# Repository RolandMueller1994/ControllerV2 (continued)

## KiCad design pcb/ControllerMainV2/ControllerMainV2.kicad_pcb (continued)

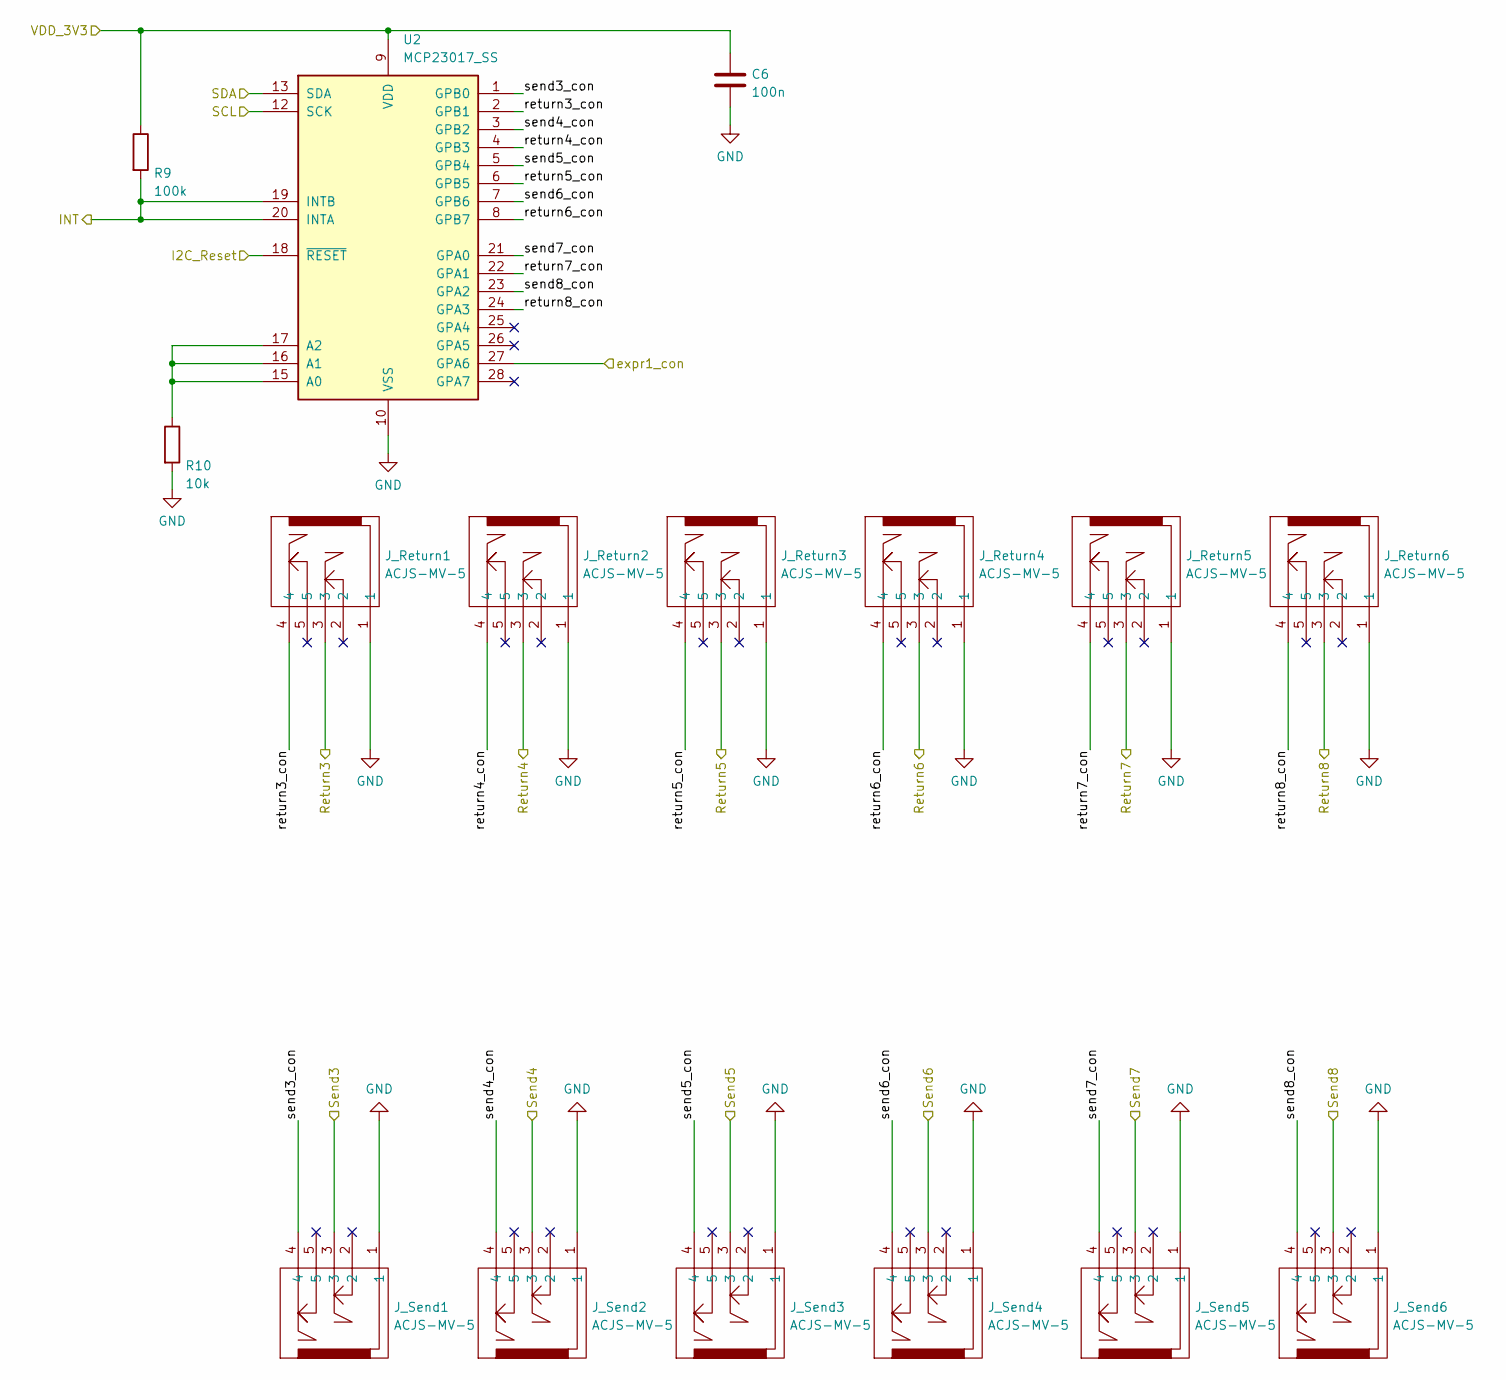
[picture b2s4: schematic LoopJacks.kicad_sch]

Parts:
C6: 100n; C_1206_3216Metric_Pad1.33x1.80mm_HandSolder
J_Return1, J_Return2, J_Return3, J_Return4, J_Return5, J_Return6: ACJS-MV-5; ACJSMV5; Manufacturer_Part_Number ACJS-MV-5; Mouser Part Number 523-ACJS-MV-5
J_Send1, J_Send2, J_Send3, J_Send4, J_Send5, J_Send6: ACJS-MV-5; ACJSMV5; Manufacturer_Part_Number ACJS-MV-5; Mouser Part Number 523-ACJS-MV-5
R9: 100k; R_0805_2012Metric_Pad1.20x1.40mm_HandSolder
R10: 10k; R_0805_2012Metric_Pad1.20x1.40mm_HandSolder
U2: MCP23017_SS; SSOP-28_5.3x10.2mm_P0.65mm

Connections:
/I2C_Reset: U2.18 (~RESET); also elsewhere on the board
/INT: R9.2, U2.19 (INTB), U2.20 (INTA); also elsewhere on the board
/LoopJacks/expr1_con: U2.27 (GPA6); also elsewhere on the board
/LoopJacks/return3_con: J_Return1.4, U2.2 (GPB1)
/LoopJacks/return4_con: J_Return2.4, U2.4 (GPB3)
/LoopJacks/return5_con: J_Return3.4, U2.6 (GPB5)
/LoopJacks/return6_con: J_Return4.4, U2.8 (GPB7)
/LoopJacks/return7_con: J_Return5.4, U2.22 (GPA1)
/LoopJacks/return8_con: J_Return6.4, U2.24 (GPA3)
/LoopJacks/send3_con: J_Send1.4, U2.1 (GPB0)
/LoopJacks/send4_con: J_Send2.4, U2.3 (GPB2)
/LoopJacks/send5_con: J_Send3.4, U2.5 (GPB4)
/LoopJacks/send6_con: J_Send4.4, U2.7 (GPB6)
/LoopJacks/send7_con: J_Send5.4, U2.21 (GPA0)
/LoopJacks/send8_con: J_Send6.4, U2.23 (GPA2)
/SCL: U2.12 (SCK); also elsewhere on the board
/SDA: U2.13 (SDA); also elsewhere on the board
/VDD_3V3: C6.1, R9.1, U2.9 (VDD); also elsewhere on the board
/return3: J_Return1.3; also elsewhere on the board
/return4: J_Return2.3; also elsewhere on the board
/return5: J_Return3.3; also elsewhere on the board
/return6: J_Return4.3; also elsewhere on the board
/return7: J_Return5.3; also elsewhere on the board
/return8: J_Return6.3; also elsewhere on the board
/send3: J_Send1.3; also elsewhere on the board
/send4: J_Send2.3; also elsewhere on the board
/send5: J_Send3.3; also elsewhere on the board
/send6: J_Send4.3; also elsewhere on the board
/send7: J_Send5.3; also elsewhere on the board
/send8: J_Send6.3; also elsewhere on the board
GND: C6.2, J_Return1.1, J_Return2.1, J_Return3.1, J_Return4.1, J_Return5.1, J_Return6.1, J_Send1.1, J_Send2.1, J_Send3.1, J_Send4.1, J_Send5.1, J_Send6.1, R10.2, U2.10 (VSS); also elsewhere on the board
unnamed: R10.1, U2.15 (A0), U2.16 (A1), U2.17 (A2)

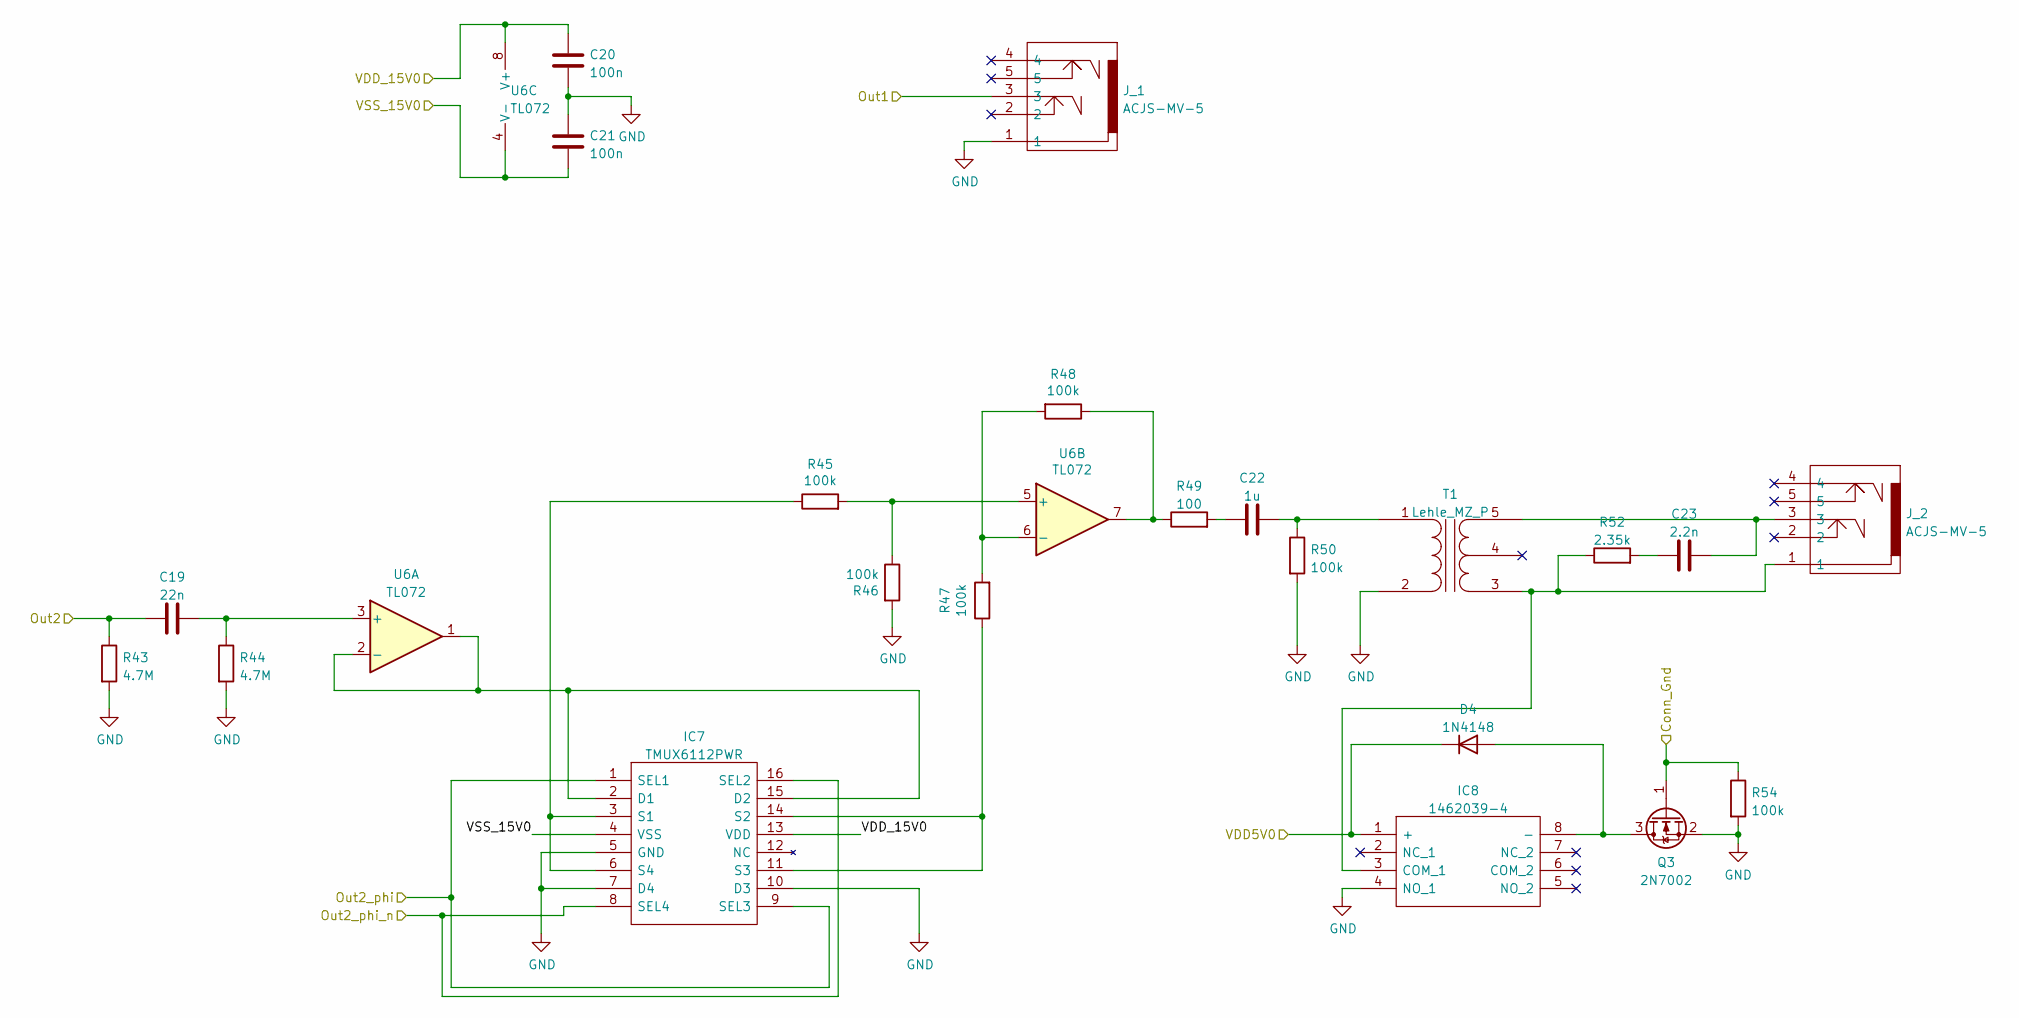
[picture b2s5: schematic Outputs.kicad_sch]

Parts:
C19: 22n; C_1206_3216Metric_Pad1.33x1.80mm_HandSolder
C20, C21: 100n; C_1206_3216Metric_Pad1.33x1.80mm_HandSolder
C22: 1u; C_1206_3216Metric_Pad1.33x1.80mm_HandSolder
C23: 2.2n; C_1206_3216Metric_Pad1.33x1.80mm_HandSolder
D4: 1N4148; D_SOD-123
IC7: TMUX6112PWR; SOP65P640X120-16N; Manufacturer_Part_Number TMUX6112PWR; Mouser Part Number 595-TMUX6112PWR
IC8: 1462039-4; 14620394; Manufacturer_Part_Number 1462039-4; Mouser Part Number 655-1462039-4
J_1, J_2: ACJS-MV-5; ACJSMV5; Manufacturer_Part_Number ACJS-MV-5; Mouser Part Number 523-ACJS-MV-5
Q3: 2N7002; SOT-23
R43, R44: 4.7M; R_0805_2012Metric_Pad1.20x1.40mm_HandSolder
R45, R46, R47, R48, R50, R54: 100k; R_0805_2012Metric_Pad1.20x1.40mm_HandSolder
R49: 100; R_0805_2012Metric_Pad1.20x1.40mm_HandSolder
R52: 2.35k; R_0805_2012Metric_Pad1.20x1.40mm_HandSolder
T1: Lehle_MZ_P
U6: TL072; SOIC-8_3.9x4.9mm_P1.27mm

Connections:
/ConnGnd: Q3.1 (G), R54.1; also elsewhere on the board
/Out2_phi: IC7.1 (SEL1), IC7.9 (SEL3); also elsewhere on the board
/Out2_phi_n: IC7.8 (SEL4), IC7.16 (SEL2); also elsewhere on the board
/VDD_5V0: D4.1 (K), IC8.1 (+); also elsewhere on the board
/VDD_15V0: C20.2, IC7.13 (VDD), U6.8 (V+); also elsewhere on the board
/VSS_15V0: C21.1, IC7.4 (VSS), U6.4 (V-); also elsewhere on the board
/out1: J_1.3; also elsewhere on the board
/out2: C19.1, R43.1; also elsewhere on the board
GND: C20.1, C21.2, IC7.5 (GND), IC7.7 (D4), IC7.10 (D3), IC8.4 (NO_1), J_1.1, Q3.2 (S), R43.2, R44.2, R46.2, R50.2, R54.2, T1.2 (AB); also elsewhere on the board
unnamed: C19.2, R44.1, U6.3 (+)
unnamed: C22.1, R49.2
unnamed: C22.2, R50.1, T1.1 (AA)
unnamed: C23.1, J_2.3, T1.5 (SB)
unnamed: C23.2, R52.2
unnamed: D4.2 (A), IC8.8 (-), Q3.3 (D)
unnamed: IC7.3 (S1), IC7.6 (S4), R45.1
unnamed: IC7.11 (S3), IC7.14 (S2), R47.1
unnamed: IC7.2 (D1), IC7.15 (D2), U6.1, U6.2 (-)
unnamed: IC8.3 (COM_1), J_2.1, R52.1, T1.3 (SA)
unnamed: R45.2, R46.1, U6.5 (+)
unnamed: R47.2, R48.2, U6.6 (-)
unnamed: R48.1, R49.1, U6.7

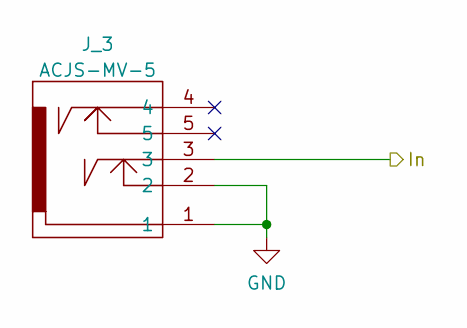
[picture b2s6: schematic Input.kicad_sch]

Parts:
J_3: ACJS-MV-5; ACJSMV5; Manufacturer_Part_Number ACJS-MV-5; Mouser Part Number 523-ACJS-MV-5

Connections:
/in: J_3.3; also elsewhere on the board
GND: J_3.1, J_3.2; also elsewhere on the board

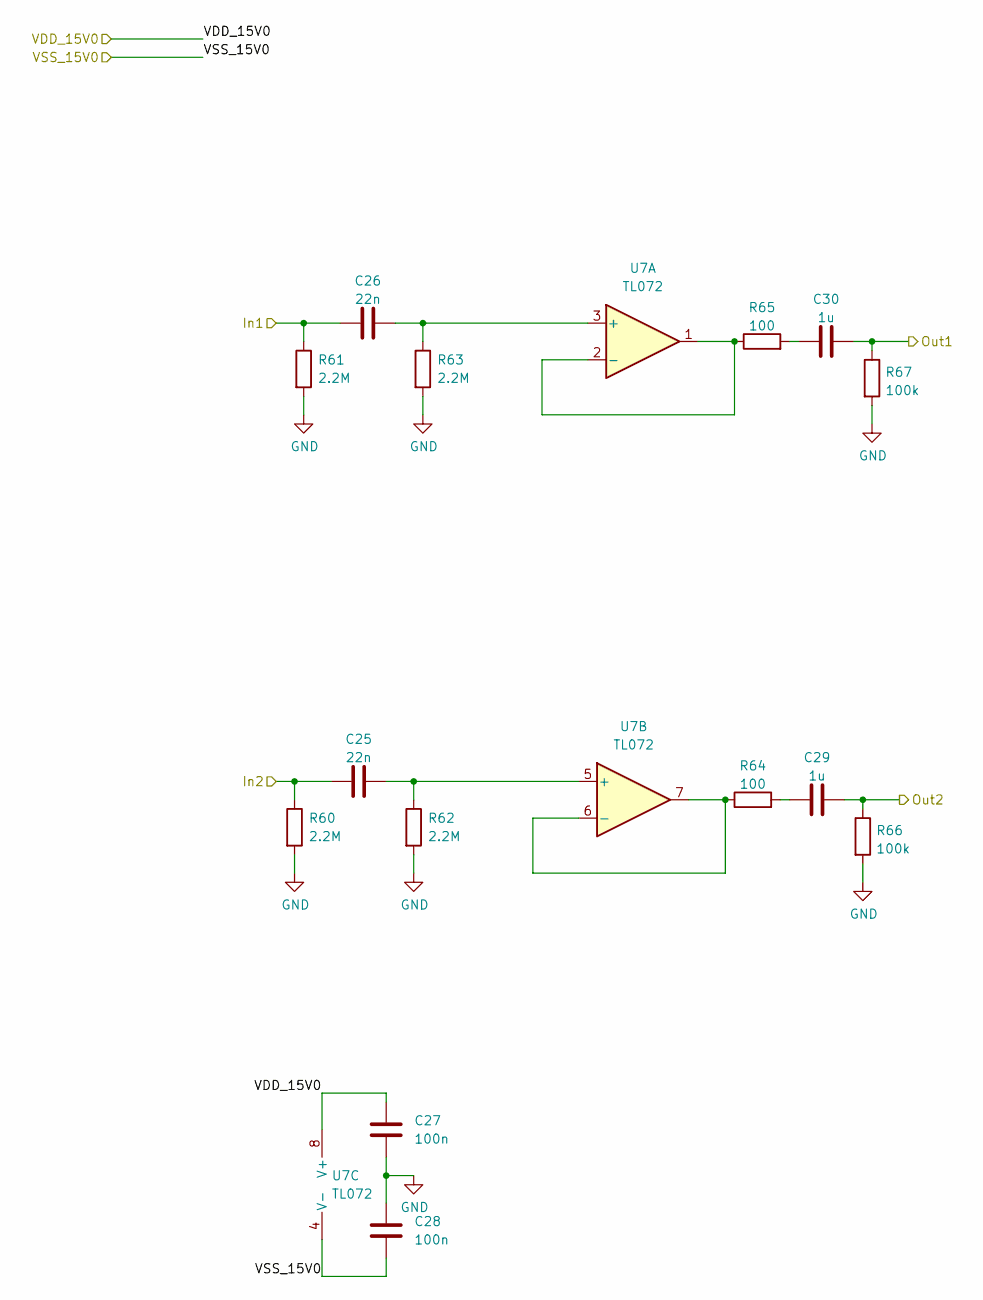
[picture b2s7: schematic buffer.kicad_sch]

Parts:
C25, C26: 22n; C_1206_3216Metric_Pad1.33x1.80mm_HandSolder
C27, C28: 100n; C_1206_3216Metric_Pad1.33x1.80mm_HandSolder
C29, C30: 1u; C_1206_3216Metric_Pad1.33x1.80mm_HandSolder
R60, R61, R62, R63: 2.2M; R_0805_2012Metric_Pad1.20x1.40mm_HandSolder
R64, R65: 100; R_0805_2012Metric_Pad1.20x1.40mm_HandSolder
R66, R67: 100k; R_0805_2012Metric_Pad1.20x1.40mm_HandSolder
U7: TL072; SOIC-8_3.9x4.9mm_P1.27mm

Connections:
/VDD_15V0: C27.2, U7.8 (V+); also elsewhere on the board
/VSS_15V0: C28.1, U7.4 (V-); also elsewhere on the board
/amp1: C26.1, R61.1; also elsewhere on the board
/amp1_out: C30.2, R67.1; also elsewhere on the board
/amp2: C25.1, R60.1; also elsewhere on the board
/amp2_out: C29.2, R66.1; also elsewhere on the board
GND: C27.1, C28.2, R60.2, R61.2, R62.2, R63.2, R66.2, R67.2; also elsewhere on the board
unnamed: C25.2, R62.1, U7.5 (+)
unnamed: C26.2, R63.1, U7.3 (+)
unnamed: C29.1, R64.2
unnamed: C30.1, R65.2
unnamed: R64.1, U7.6 (-), U7.7
unnamed: R65.1, U7.1, U7.2 (-)

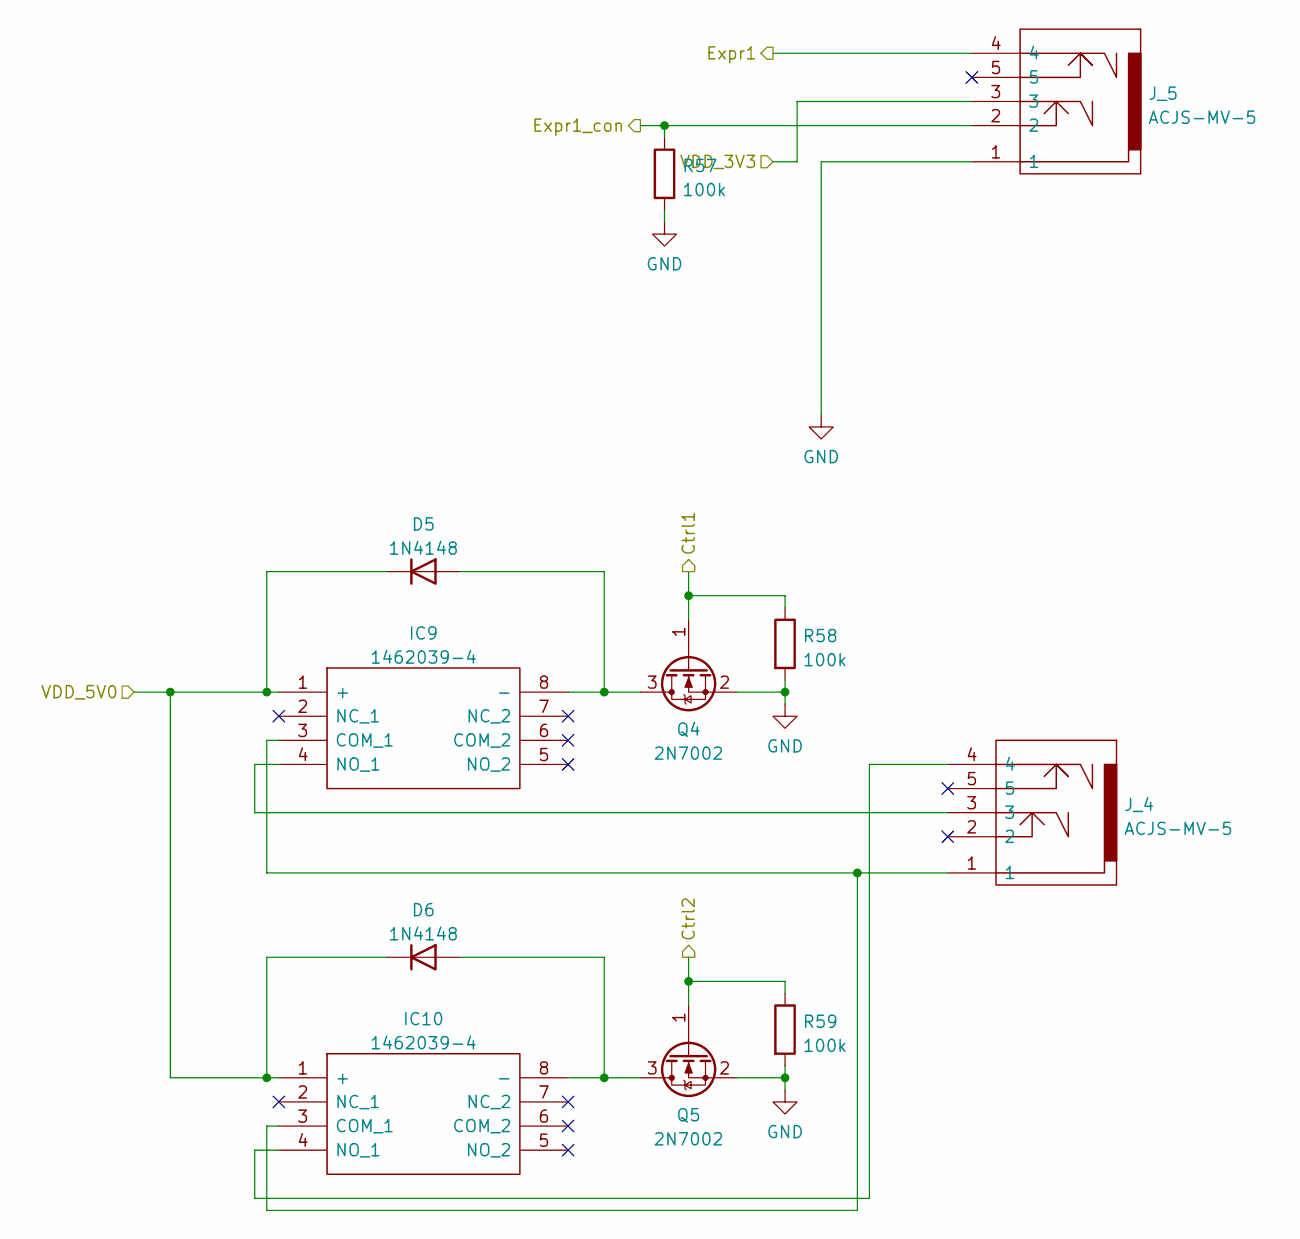
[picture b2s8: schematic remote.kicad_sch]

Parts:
D5, D6: 1N4148; D_SOD-123
IC9, IC10: 1462039-4; 14620394; Manufacturer_Part_Number 1462039-4; Mouser Part Number 655-1462039-4
J_4, J_5: ACJS-MV-5; ACJSMV5; Manufacturer_Part_Number ACJS-MV-5; Mouser Part Number 523-ACJS-MV-5
Q4, Q5: 2N7002; SOT-23
R57, R58, R59: 100k; R_0805_2012Metric_Pad1.20x1.40mm_HandSolder

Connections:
/Ctrl1: Q4.1 (G), R58.1; also elsewhere on the board
/Ctrl2: Q5.1 (G), R59.1; also elsewhere on the board
/LoopJacks/expr1_con: J_5.2, R57.1; also elsewhere on the board
/VDD_3V3: J_5.3; also elsewhere on the board
/VDD_5V0: D5.1 (K), D6.1 (K), IC9.1 (+), IC10.1 (+); also elsewhere on the board
/expr1: J_5.4; also elsewhere on the board
GND: J_5.1, Q4.2 (S), Q5.2 (S), R57.2, R58.2, R59.2; also elsewhere on the board
unnamed: D5.2 (A), IC9.8 (-), Q4.3 (D)
unnamed: D6.2 (A), IC10.8 (-), Q5.3 (D)
unnamed: IC9.4 (NO_1), J_4.3
unnamed: IC9.3 (COM_1), IC10.3 (COM_1), J_4.1
unnamed: IC10.4 (NO_1), J_4.4

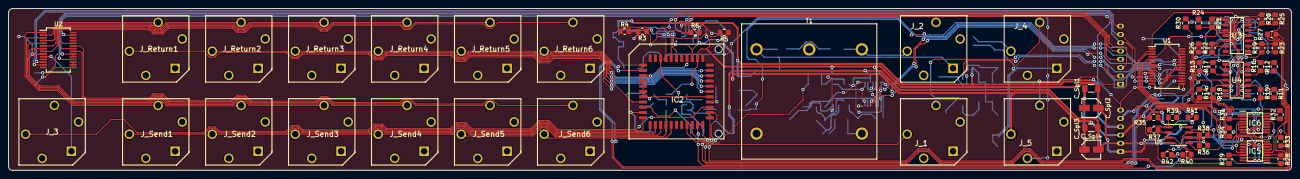
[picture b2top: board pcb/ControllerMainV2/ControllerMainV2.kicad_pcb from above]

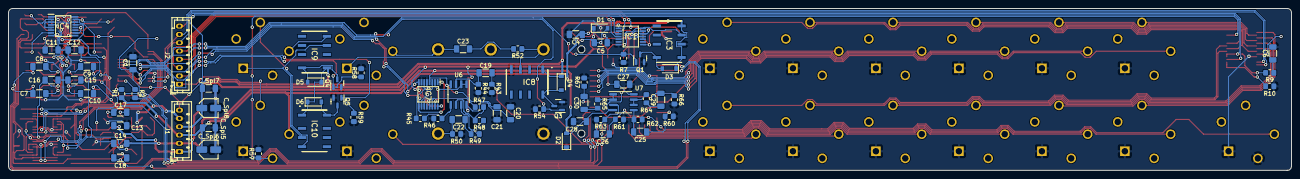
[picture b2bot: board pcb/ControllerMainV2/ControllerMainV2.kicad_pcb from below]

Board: 2 copper layers, 309.2 x 39.0 mm, 144 parts (78 on the bottom side), 128 nets.

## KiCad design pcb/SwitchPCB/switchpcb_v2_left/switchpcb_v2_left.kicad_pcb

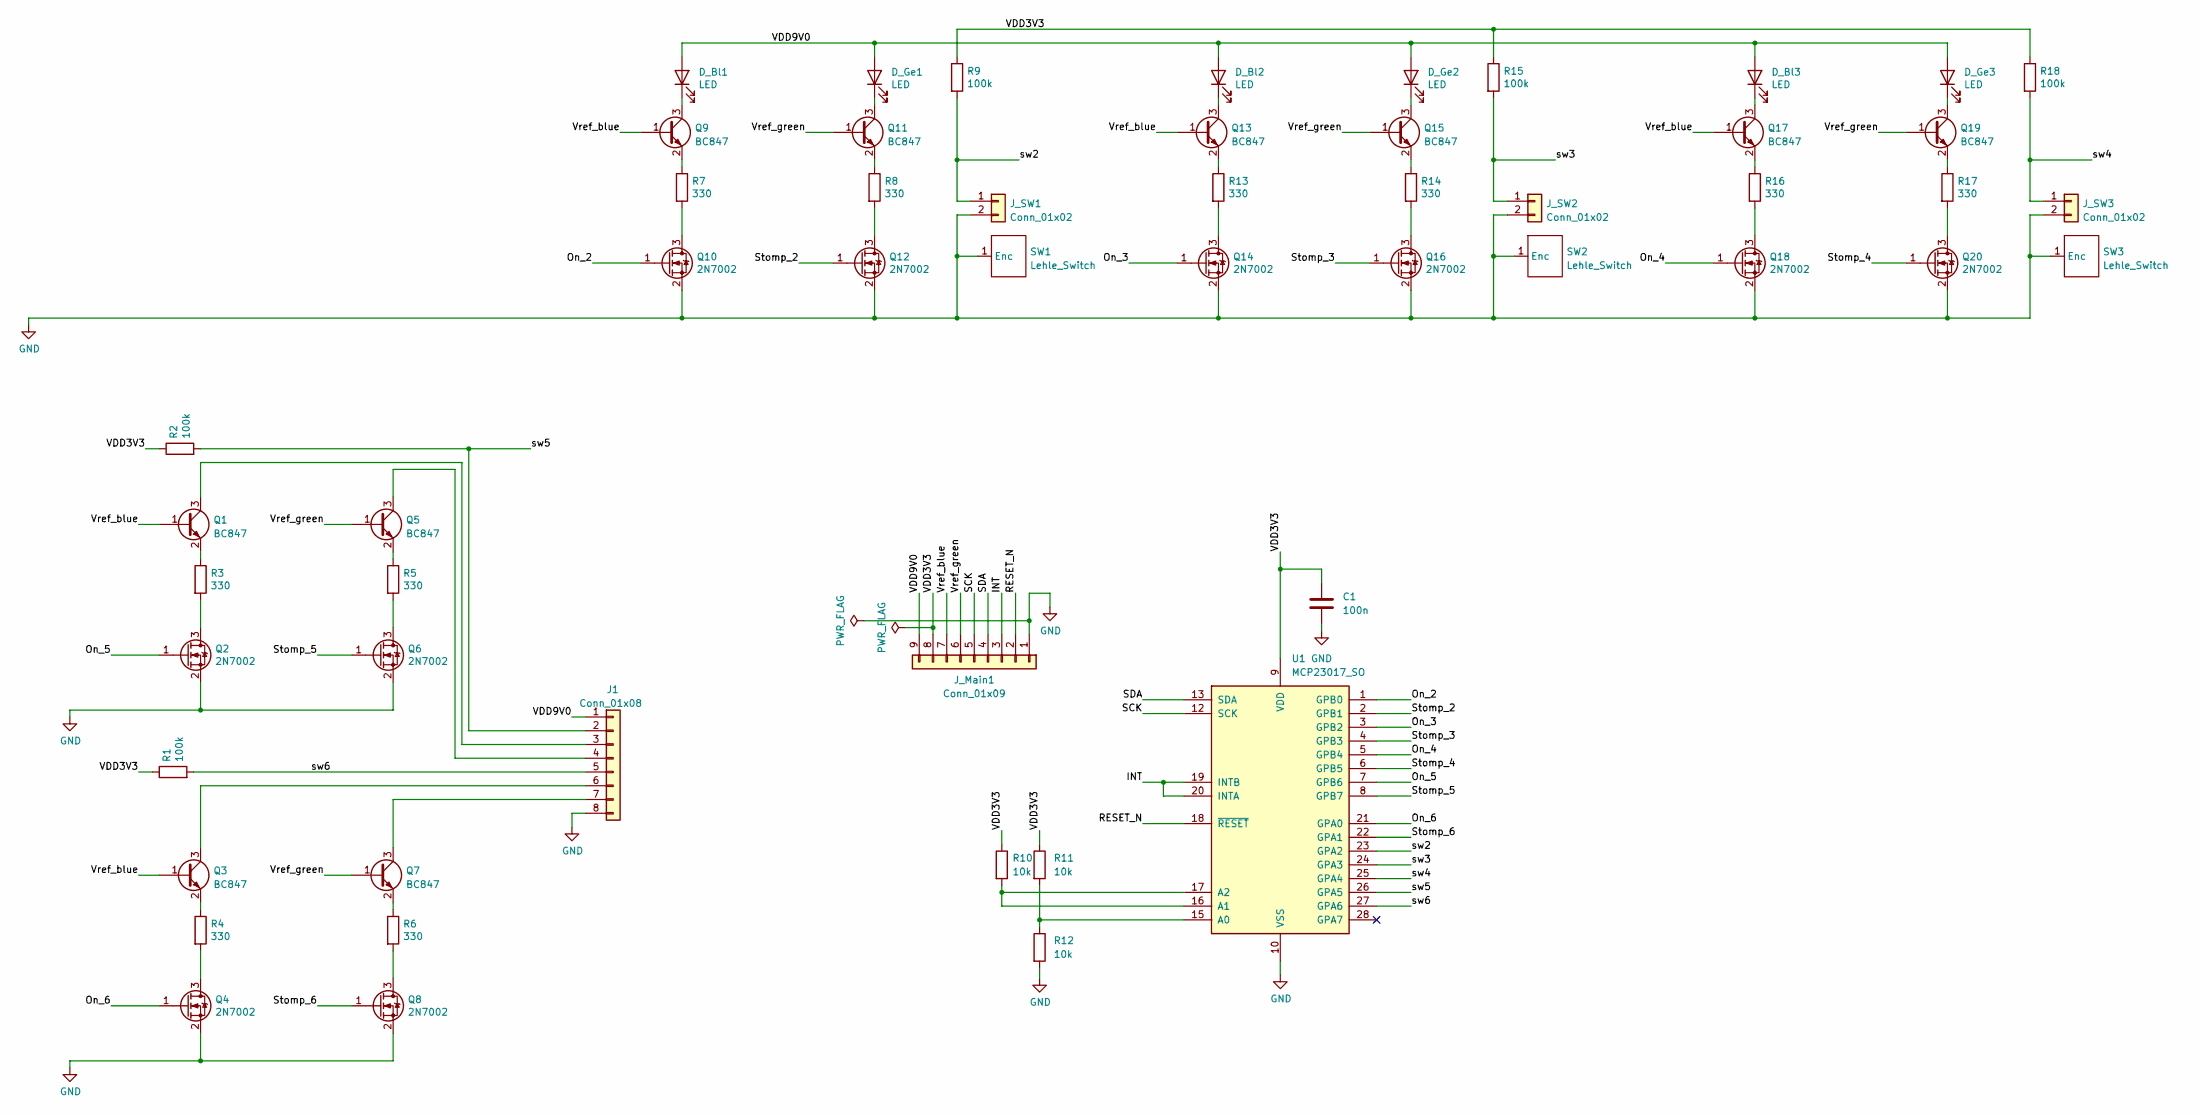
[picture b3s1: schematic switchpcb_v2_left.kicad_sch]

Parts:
C1: 100n; C_1206_3216Metric_Pad1.33x1.80mm_HandSolder
D_Bl1, D_Bl2, D_Bl3: LED; LED_D3.0mm
D_Ge1, D_Ge2, D_Ge3: LED; LED_D3.0mm
J1: Conn_01x08; JST_PH_B8B-PH-K_1x08_P2.00mm_Vertical
J_Main1: Conn_01x09; JST_PH_B9B-PH-K_1x09_P2.00mm_Vertical
J_SW1, J_SW2, J_SW3: Conn_01x02; JST_PH_B2B-PH-K_1x02_P2.00mm_Vertical
Q1, Q3, Q5, Q7, Q9, Q11, Q13, Q15, Q17, Q19: BC847; SOT-23
Q2, Q4, Q6, Q8, Q10, Q12, Q14, Q16, Q18, Q20: 2N7002; SOT-23
R1, R2, R9, R15, R18: 100k; R_0805_2012Metric_Pad1.20x1.40mm_HandSolder
R3, R4, R5, R6, R7, R8, R13, R14, R16, R17: 330; R_0805_2012Metric_Pad1.20x1.40mm_HandSolder
R10, R11, R12: 10k; R_0805_2012Metric_Pad1.20x1.40mm_HandSolder
SW1, SW2, SW3: Lehle_Switch; LehleSwitch
U1: MCP23017_SO; SOIC-28W_7.5x17.9mm_P1.27mm

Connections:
/INT: J_Main1.3, U1.19 (INTB), U1.20 (INTA)
/On_2: Q10.1 (G), U1.1 (GPB0)
/On_3: Q14.1 (G), U1.3 (GPB2)
/On_4: Q18.1 (G), U1.5 (GPB4)
/On_5: Q2.1 (G), U1.7 (GPB6)
/On_6: Q4.1 (G), U1.21 (GPA0)
/RESET_N: J_Main1.2, U1.18 (~RESET)
/SCK: J_Main1.5, U1.12 (SCK)
/SDA: J_Main1.4, U1.13 (SDA)
/Stomp_2: Q12.1 (G), U1.2 (GPB1)
/Stomp_3: Q16.1 (G), U1.4 (GPB3)
/Stomp_4: Q20.1 (G), U1.6 (GPB5)
/Stomp_5: Q6.1 (G), U1.8 (GPB7)
/Stomp_6: Q8.1 (G), U1.22 (GPA1)
/VDD3V3: C1.1, J_Main1.8, R1.1, R2.1, R9.1, R10.1, R11.1, R15.1, R18.1, U1.9 (VDD)
/VDD9V0: D_Bl1.2 (A), D_Bl2.2 (A), D_Bl3.2 (A), D_Ge1.2 (A), D_Ge2.2 (A), D_Ge3.2 (A), J1.1, J_Main1.9
/Vref_blue: J_Main1.7, Q1.1 (B), Q3.1 (B), Q9.1 (B), Q13.1 (B), Q17.1 (B)
/Vref_green: J_Main1.6, Q5.1 (B), Q7.1 (B), Q11.1 (B), Q15.1 (B), Q19.1 (B)
/sw2: J_SW1.1, R9.2, U1.23 (GPA2)
/sw3: J_SW2.1, R15.2, U1.24 (GPA3)
/sw4: J_SW3.1, R18.2, U1.25 (GPA4)
/sw5: J1.2, R2.2, U1.26 (GPA5)
/sw6: J1.5, R1.2, U1.27 (GPA6)
GND: C1.2, J1.8, J_Main1.1, J_SW1.2, J_SW2.2, J_SW3.2, Q2.2 (S), Q4.2 (S), Q6.2 (S), Q8.2 (S), Q10.2 (S), Q12.2 (S), Q14.2 (S), Q16.2 (S), Q18.2 (S), Q20.2 (S), R12.2, SW1.1 (Enc), SW2.1 (Enc), SW3.1 (Enc), U1.10 (VSS)
unnamed: D_Bl1.1 (K), Q9.3 (C)
unnamed: D_Bl2.1 (K), Q13.3 (C)
unnamed: D_Bl3.1 (K), Q17.3 (C)
unnamed: D_Ge1.1 (K), Q11.3 (C)
unnamed: D_Ge2.1 (K), Q15.3 (C)
unnamed: D_Ge3.1 (K), Q19.3 (C)
unnamed: J1.3, Q1.3 (C)
unnamed: J1.4, Q5.3 (C)
unnamed: J1.6, Q3.3 (C)
unnamed: J1.7, Q7.3 (C)
unnamed: Q1.2 (E), R3.1
unnamed: Q2.3 (D), R3.2
unnamed: Q3.2 (E), R4.1
unnamed: Q4.3 (D), R4.2
unnamed: Q5.2 (E), R5.1
unnamed: Q6.3 (D), R5.2
unnamed: Q7.2 (E), R6.1
unnamed: Q8.3 (D), R6.2
unnamed: Q9.2 (E), R7.1
unnamed: Q10.3 (D), R7.2
unnamed: Q11.2 (E), R8.1
unnamed: Q12.3 (D), R8.2
unnamed: Q13.2 (E), R13.1
unnamed: Q14.3 (D), R13.2
unnamed: Q15.2 (E), R14.1
unnamed: Q16.3 (D), R14.2
unnamed: Q17.2 (E), R16.1
unnamed: Q18.3 (D), R16.2
unnamed: Q19.2 (E), R17.1
unnamed: Q20.3 (D), R17.2
unnamed: R10.2, U1.16 (A1), U1.17 (A2)
unnamed: R11.2, R12.1, U1.15 (A0)

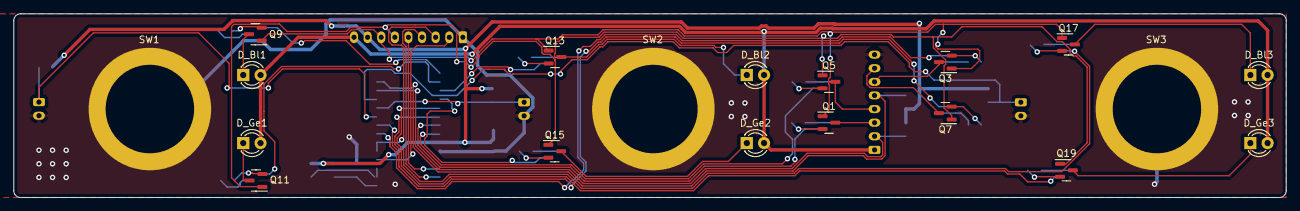
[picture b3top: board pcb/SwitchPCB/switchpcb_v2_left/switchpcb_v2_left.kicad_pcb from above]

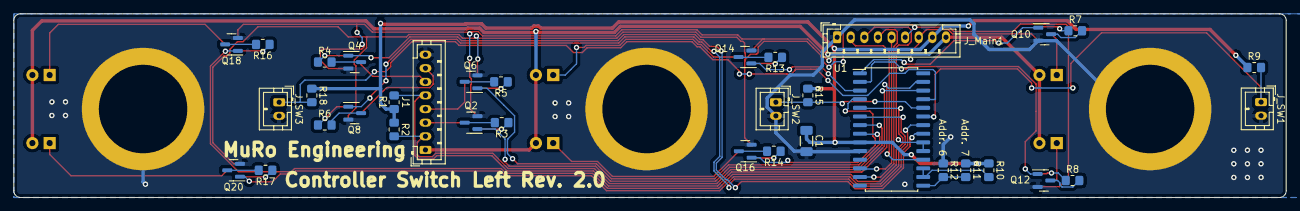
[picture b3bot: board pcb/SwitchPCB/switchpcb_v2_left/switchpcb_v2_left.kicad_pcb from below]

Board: 2 copper layers, 187.0 x 27.0 mm, 54 parts (35 on the bottom side), 56 nets.

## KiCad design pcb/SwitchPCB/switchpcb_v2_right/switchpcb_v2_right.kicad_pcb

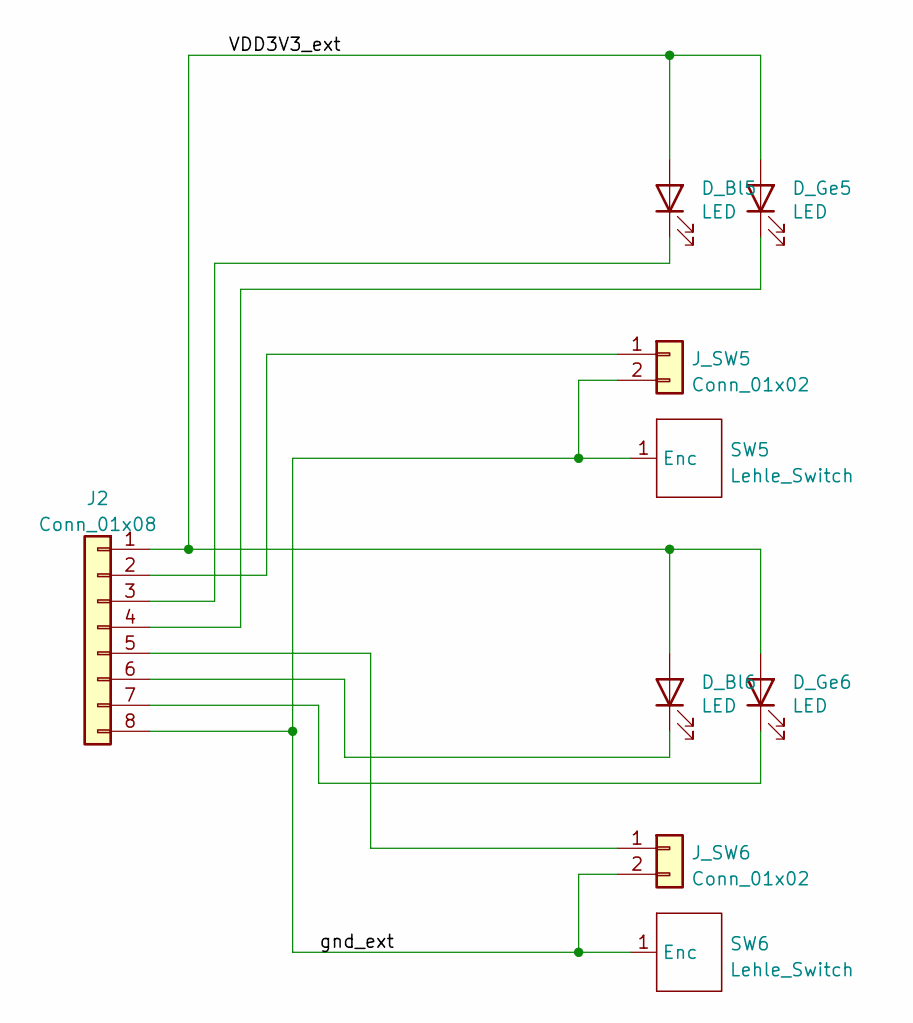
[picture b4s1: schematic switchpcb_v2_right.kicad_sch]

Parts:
D_Bl5, D_Bl6: LED; LED_D3.0mm
D_Ge5, D_Ge6: LED; LED_D3.0mm
J2: Conn_01x08; JST_PH_B8B-PH-K_1x08_P2.00mm_Vertical
J_SW5, J_SW6: Conn_01x02; JST_PH_B2B-PH-K_1x02_P2.00mm_Vertical
SW5, SW6: Lehle_Switch; LehleSwitch

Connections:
/VDD3V3_ext: D_Bl5.2 (A), D_Bl6.2 (A), D_Ge5.2 (A), D_Ge6.2 (A), J2.1
/gnd_ext: J2.8, J_SW5.2, J_SW6.2, SW5.1 (Enc), SW6.1 (Enc)
unnamed: D_Bl5.1 (K), J2.3
unnamed: D_Bl6.1 (K), J2.6
unnamed: D_Ge5.1 (K), J2.4
unnamed: D_Ge6.1 (K), J2.7
unnamed: J2.2, J_SW5.1
unnamed: J2.5, J_SW6.1

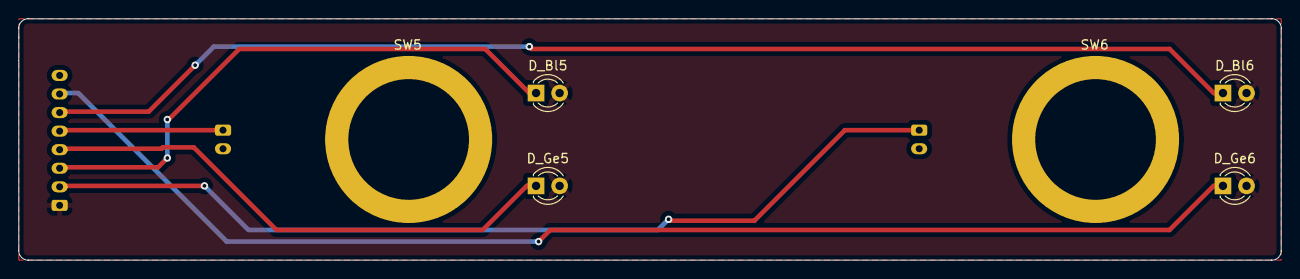
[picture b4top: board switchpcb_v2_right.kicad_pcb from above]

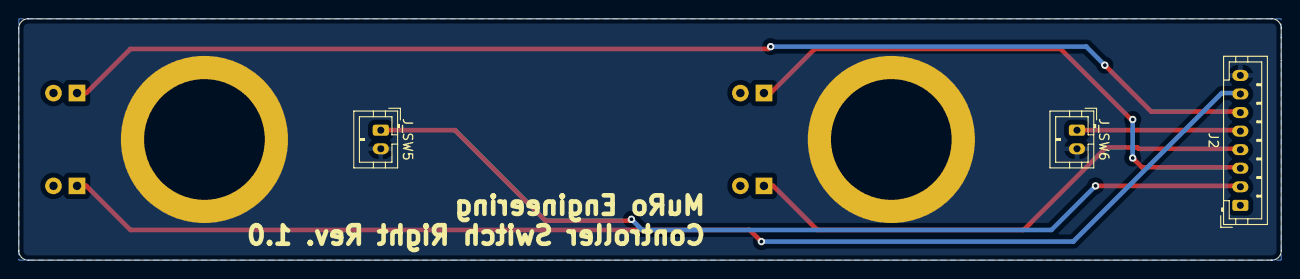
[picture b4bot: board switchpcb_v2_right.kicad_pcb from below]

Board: 2 copper layers, 136.0 x 26.0 mm, 9 parts (3 on the bottom side), 8 nets.
